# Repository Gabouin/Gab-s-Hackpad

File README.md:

# Gab-s-Hackpad
I am making my first PCB project : a simple hackpad with 6 switch, a rotary encoder, an oled display and the microcontroller.
The OLED screen will display animations based on what switch is pushed, leds will be illuminating all the macropad with predifined colors animations.The rotary encoder is going to be used to change the volume and, for the moment, the switches will regulate my spotify playlist (as I listen music while working) and other things I will decide once my hackpad is finished.

last version of my schematic on KiCad : 

PCB on KiCad :

KiCad's 3d render of it : 

PCB on Fusion 360 : 

Final model on Fusion 360 : 

Parts to 3d print : 

Bill Of Material :

https://blueprint.hackclub.com/hackpad/parts

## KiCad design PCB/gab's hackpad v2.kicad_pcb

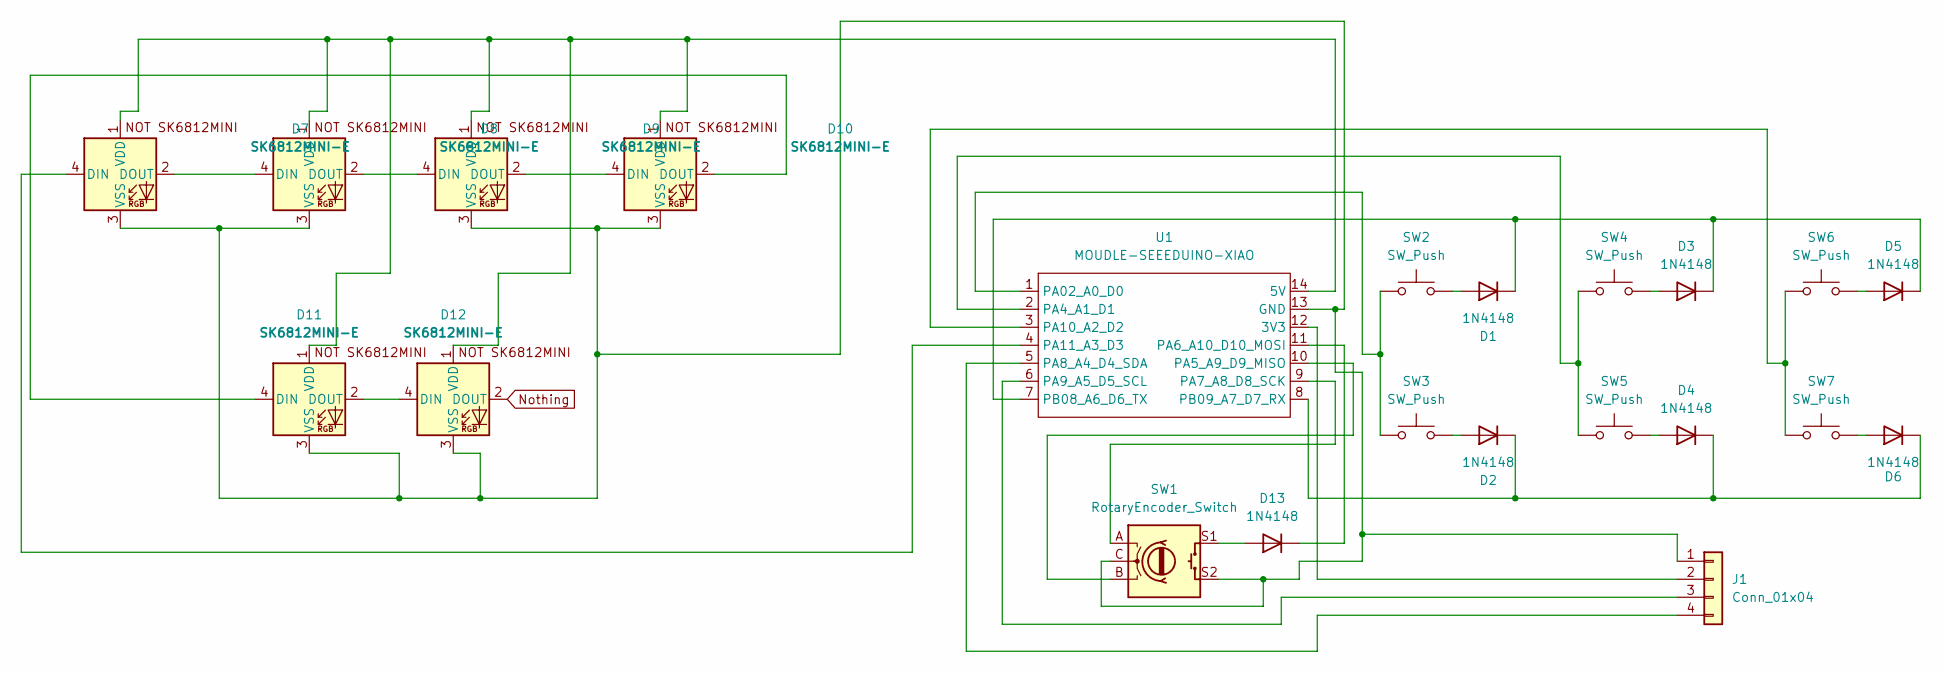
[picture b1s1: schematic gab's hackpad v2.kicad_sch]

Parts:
D1, D2, D3, D4, D5, D6, D13: 1N4148; D_DO-35_SOD27_P7.62mm_Horizontal
D7, D8, D9, D10, D11, D12: SK6812MINI-E; SK6812MINI-E_fixed
J1: Conn_01x04; OLED_0.91_128x32
SW1: RotaryEncoder_Switch; RotaryEncoder_Alps_EC11E-Switch_Vertical_H20mm
SW2, SW3, SW4, SW5, SW6, SW7: SW_Push; SW_Cherry_MX_1.00u_PCB
U1: MOUDLE-SEEEDUINO-XIAO; XIAO-RP2040-DIP

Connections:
unnamed: D1.2 (A), SW2.2
unnamed: D1.1 (K), D3.1 (K), D5.1 (K), U1.7 (PB08_A6_D6_TX)
unnamed: D2.2 (A), SW3.2
unnamed: D2.1 (K), D4.1 (K), D6.1 (K), U1.8 (PB09_A7_D7_RX)
unnamed: D3.2 (A), SW4.2
unnamed: D4.2 (A), SW5.2
unnamed: D5.2 (A), SW6.2
unnamed: D6.2 (A), SW7.2
unnamed: D7.4 (DIN), U1.4 (PA11_A3_D3)
unnamed: D7.2 (DOUT), D8.4 (DIN)
unnamed: D8.2 (DOUT), D9.4 (DIN)
unnamed: D9.2 (DOUT), D10.4 (DIN)
unnamed: D10.2 (DOUT), D11.4 (DIN)
unnamed: D7.1 (VDD), D8.1 (VDD), D9.1 (VDD), D10.1 (VDD), D11.1 (VDD), D12.1 (VDD), U1.14 (5V)
unnamed: D7.3 (VSS), D8.3 (VSS), D9.3 (VSS), D10.3 (VSS), D11.3 (VSS), D12.3 (VSS), J1.1, SW1.C, SW1.S2, U1.13 (GND)
unnamed: D11.2 (DOUT), D12.4 (DIN)
unnamed: D13.2 (A), SW1.S1
unnamed: D13.1 (K), U1.11 (PA6_A10_D10_MOSI)
unnamed: J1.2, U1.12 (3V3)
unnamed: J1.3, U1.6 (PA9_A5_D5_SCL)
unnamed: J1.4, U1.5 (PA8_A4_D4_SDA)
unnamed: SW2.1, SW3.1, U1.1 (PA02_A0_D0)
unnamed: SW4.1, SW5.1, U1.2 (PA4_A1_D1)
unnamed: SW1.B, U1.10 (PA5_A9_D9_MISO)
unnamed: SW1.A, U1.9 (PA7_A8_D8_SCK)
unnamed: SW6.1, SW7.1, U1.3 (PA10_A2_D2)
Nothing: D12.2 (DOUT)

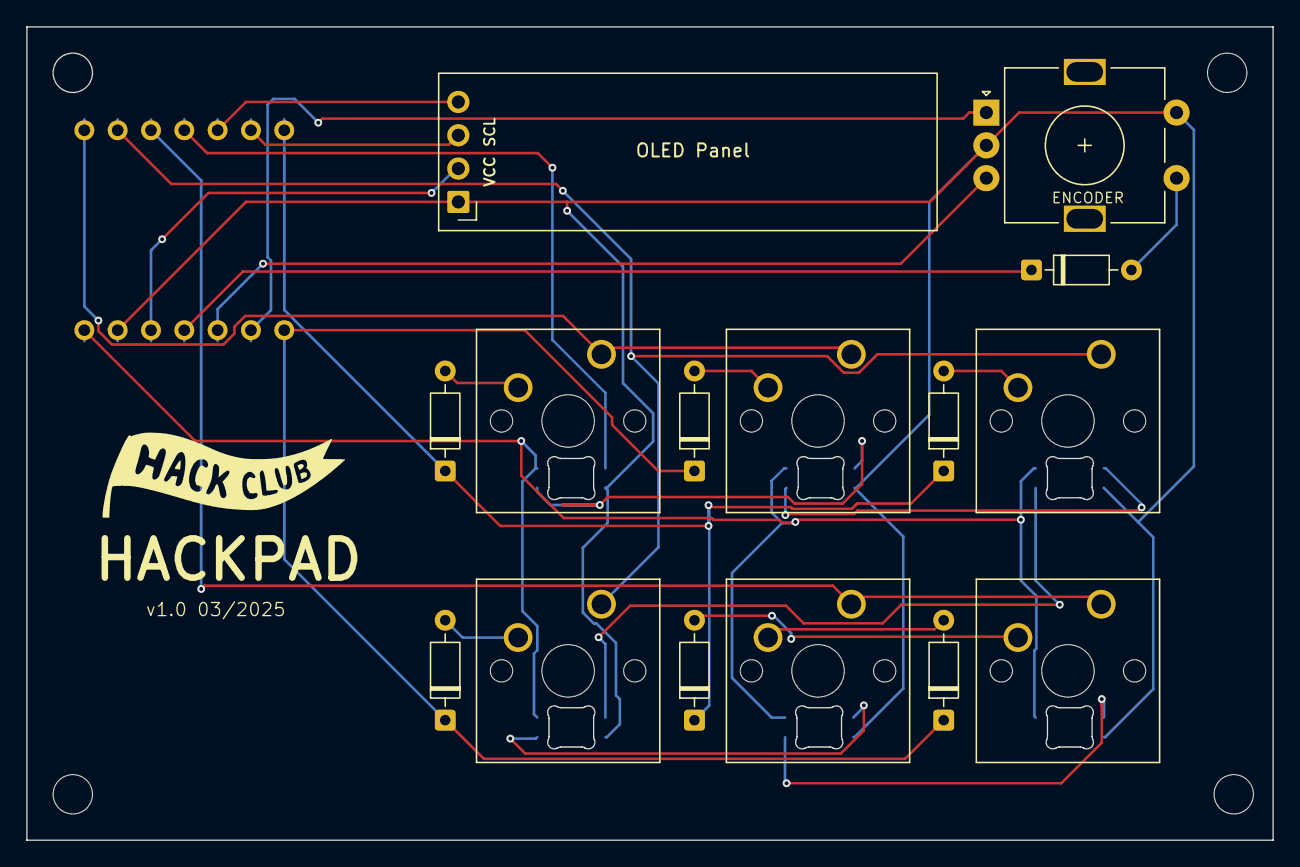
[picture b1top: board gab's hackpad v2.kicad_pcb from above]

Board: 2 copper layers, 95.0 x 62.0 mm, 22 parts (1 on the bottom side), 26 nets.

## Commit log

2026-03-07 Add final model images to README
    Added final model images from Fusion 360 to the README.
2026-03-07 Update README with images and 3D print parts
    Added images and parts list for 3D printing.
2026-03-08 Rename gab's hackpad.step to CAD/gab's hackpad.step
2026-03-08 Rename oled_display.c to FIRMWARE/oled_display.c
2026-03-08 Rename info.json to FIRMWARE/info.json
2026-03-08 Rename config.h to FIRMWARE/config.h
2026-03-08 Rename FLASH_INSTRUCTIONS.md to FIRMWARE/FLASH_INSTRUCTIONS.md
2026-03-08 Add link to Hack Club parts blueprint
2026-03-08 Rename hackpad-job.zip to PRODUCTION/hackpad-job.zip
2026-03-10 Rename gab's hackpad v2.step to CAD/gab's hackpad v2.step
2026-03-10 Rename gab's hackpad v2 CAD.zip to CAD/gab's hackpad v2 CAD.zip
